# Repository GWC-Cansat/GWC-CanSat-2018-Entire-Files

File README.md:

# GWC CanSat 2017-2018 Files
All completed files used for the 2018 GWC CanSat entry.

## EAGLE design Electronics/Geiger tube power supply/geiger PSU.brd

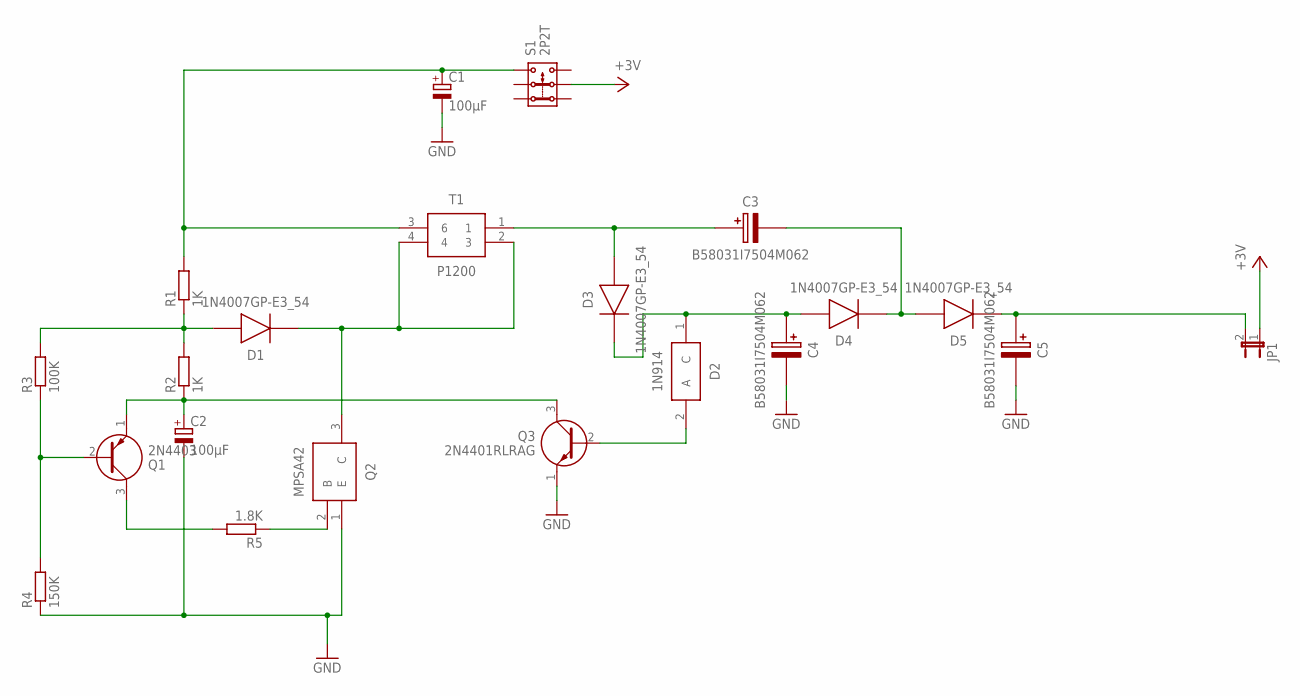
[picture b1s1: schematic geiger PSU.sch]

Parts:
C1, C2: 100μF; 085CS_1AR
C3, C4, C5: B58031I7504M062; CAPPC10878X450N
D1, D3, D4, D5: 1N4007GP-E3_54; DIOAD1405W86L465D235
D2: 1N914; DIO_1N914
JP1: JP1E; JP1
Q1: 2N4403; TO160P419X482X533-3P
Q2: MPSA42; TO127P254X635-3
Q3: 2N4401RLRAG; TO-92
R1, R2: 1K; 0204V
R3: 100K; 0204V
R4: 150K; 0204V
R5: 1.8K; 0204V
S1: 2P2T
T1: P1200; HDRV4W100P762X1270_2X2_1800X18

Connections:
GND: C1.-, C2.-, C4.2 (-), C5.2 (-), Q2.1 (E), Q3.1 (E), R4.1
unnamed: C1.+, R1.2, S1.3.1, T1.3 (6)
unnamed: D1.2 (A), R1.1, R2.2, R3.2
unnamed: Q1.2 (B), R3.1, R4.2
unnamed: C2.+, Q1.1 (E), Q3.3 (C), R2.1
unnamed: Q1.3 (C), R5.2
unnamed: D1.1 (K), Q2.3 (C), T1.2 (3), T1.4
unnamed: C3.1 (+), D3.2 (A), T1.1
unnamed: Q2.2 (B), R5.1
unnamed: D2.2 (A), Q3.2 (B)
unnamed: C4.1 (+), D2.1 (C), D3.1 (K), D4.2 (A)
unnamed: C3.2 (-), D4.1 (K), D5.2 (A)
unnamed: C5.1 (+), D5.1 (K), JP1.2
VCC: JP1.1, S1.2.2

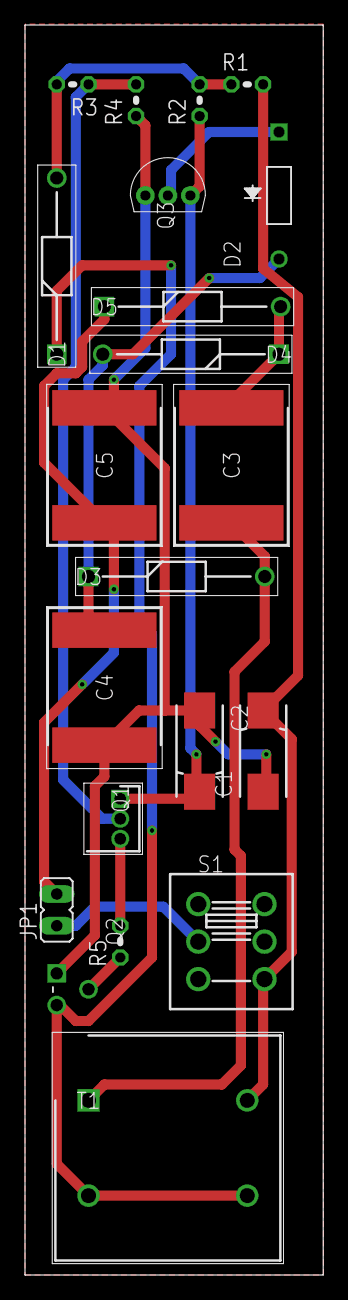
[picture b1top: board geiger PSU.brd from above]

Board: 2 copper layers, 23.9 x 100.0 mm, 21 parts (0 on the bottom side), 14 nets.

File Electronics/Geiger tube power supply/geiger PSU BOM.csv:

"Qty";"Value";"Device";"Package";"Parts";"Description";"3D_PACKAGE";"ALLIED_NUMBER";"DESCRIPTION";"HEIGHT";"MANUFACTURER_NAME";"MANUFACTURER_PART_NUMBER";"OTHER_PART_NUMBER";"RS_PART_NUMBER";"SUPPLIER_NAME";
"1";"";"JP1E";"JP1";"JP1";"JUMPER";"";"";"";"";"";"";"";"";"";
"1";"1.8K";"R-EU_0204/2V";"0204V";"R5";"RESISTOR, European symbol";"";"";"";"";"";"";"";"";"";
"1";"100K";"R-EU_0204/2V";"0204V";"R3";"RESISTOR, European symbol";"";"";"";"";"";"";"";"";"";
"2";"100µF";"CPOL-EU085CS-1AR";"085CS_1AR";"C1, C2";"POLARIZED CAPACITOR, European symbol";"";"";"";"";"";"";"";"";"";
"1";"150K";"R-EU_0204/2V";"0204V";"R4";"RESISTOR, European symbol";"";"";"";"";"";"";"";"";"";
"2";"1K";"R-EU_0204/2V";"0204V";"R1, R2";"RESISTOR, European symbol";"";"";"";"";"";"";"";"";"";
"4";"1N4007GP-E3_54";"1N4007GP-E3_54";"DIOAD1405W86L465D235";"D1, D3, D4, D5";"Vishay 1N4007GP-E3/54, Switching Diode, 1000V 1A, 2000ns, 2-Pin DO-204AL";"";"";"Vishay 1N4007GP-E3/54, Switching Diode, 1000V 1A, 2000ns, 2-Pin DO-204AL";"mm";"Vishay";"1N4007GP-E3/54";"";"7087984P";"RS";
"1";"1N914";"1N914";"DIO_1N914";"D2";"Small Signal Diode";"";"";"Small Signal Diode";"mm";"Fairchild Semiconductor";"1N914";"";"";"RS";
"1";"2N4401RLRAG";"2N4401RLRAG";"TO-92";"Q3";"Transistor NPN 40V 600mA TO92 ON Semi 2N4401RLRAG NPN Bipolar Transistor,  600 mA 40 V, 3-Pin TO-92";"";"70100181";"Transistor NPN 40V 600mA TO92 ON Semi 2N4401RLRAG NPN Bipolar Transistor,  600 mA 40 V, 3-Pin TO-92";"mm";"ON Semiconductor";"2N4401RLRAG";"";"7925476";"RS";
"1";"2N4403";"2N4403";"TO160P419X482X533-3P";"Q1";"MULTICOMP - 2N4403 - TRANSISTOR, PNP, -40V, -0.6A, TO-92";"";"";"MULTICOMP - 2N4403 - TRANSISTOR, PNP, -40V, -0.6A, TO-92";"4.19mm";"MULTICOMP";"2N4403";"";"";"RS";
"1";"2P2T";"2P2T";"2P2T";"S1";"SLIDE SWITCH 2P2T Part No. SS-22F05-G(A)4";"";"";"";"";"";"";"";"";"";
"3";"B58031I7504M062";"B58031I7504M062";"CAPPC10878X450N";"C3, C4, C5";"EPCOS - B58031I7504M062 - CAP, MLCC, AEC-Q200, 0.5UF, 700V, SMD";"";"";"EPCOS - B58031I7504M062 - CAP, MLCC, AEC-Q200, 0.5UF, 700V, SMD";"4.5mm";"EPCOS";"B58031I7504M062";"";"";"RS";
"1";"MPSA42";"MPSA42";"TO127P254X635-3";"Q2";"Transistor";"";"";"Transistor";"mm";"Fairchild Semiconductor";"MPSA42";"";"1241357";"RS";
"1";"P1200";"P1200";"HDRV4W100P762X1270_2X2_1800X18";"T1";"ETAL - P1200 - TRANSFORMER, LINE MATCHING, V.32 BIS";"";"";"ETAL - P1200 - TRANSFORMER, LINE MATCHING, V.32 BIS";"12.6mm";"ETAL";"P1200";"";"";"RS";

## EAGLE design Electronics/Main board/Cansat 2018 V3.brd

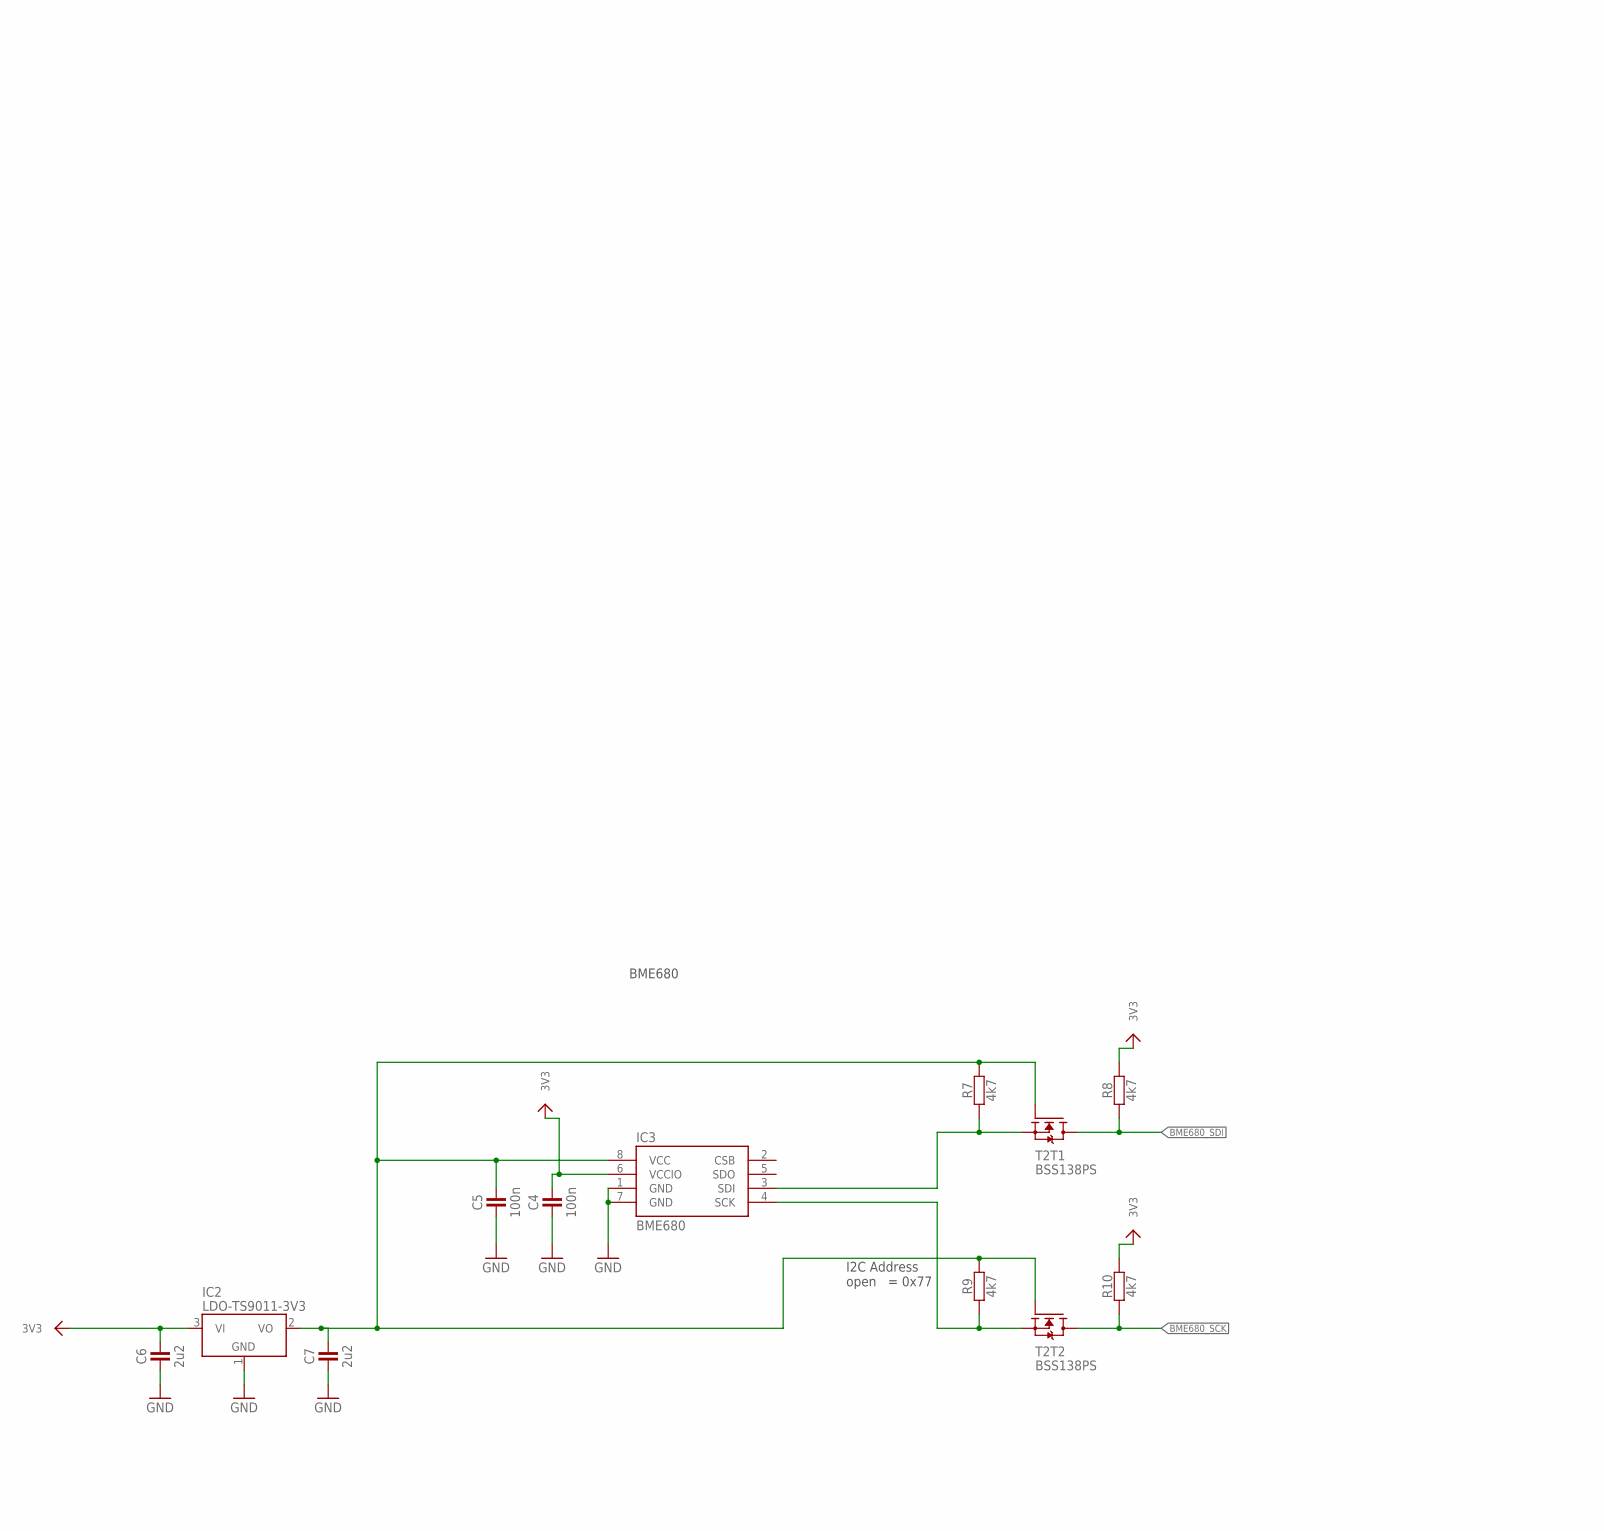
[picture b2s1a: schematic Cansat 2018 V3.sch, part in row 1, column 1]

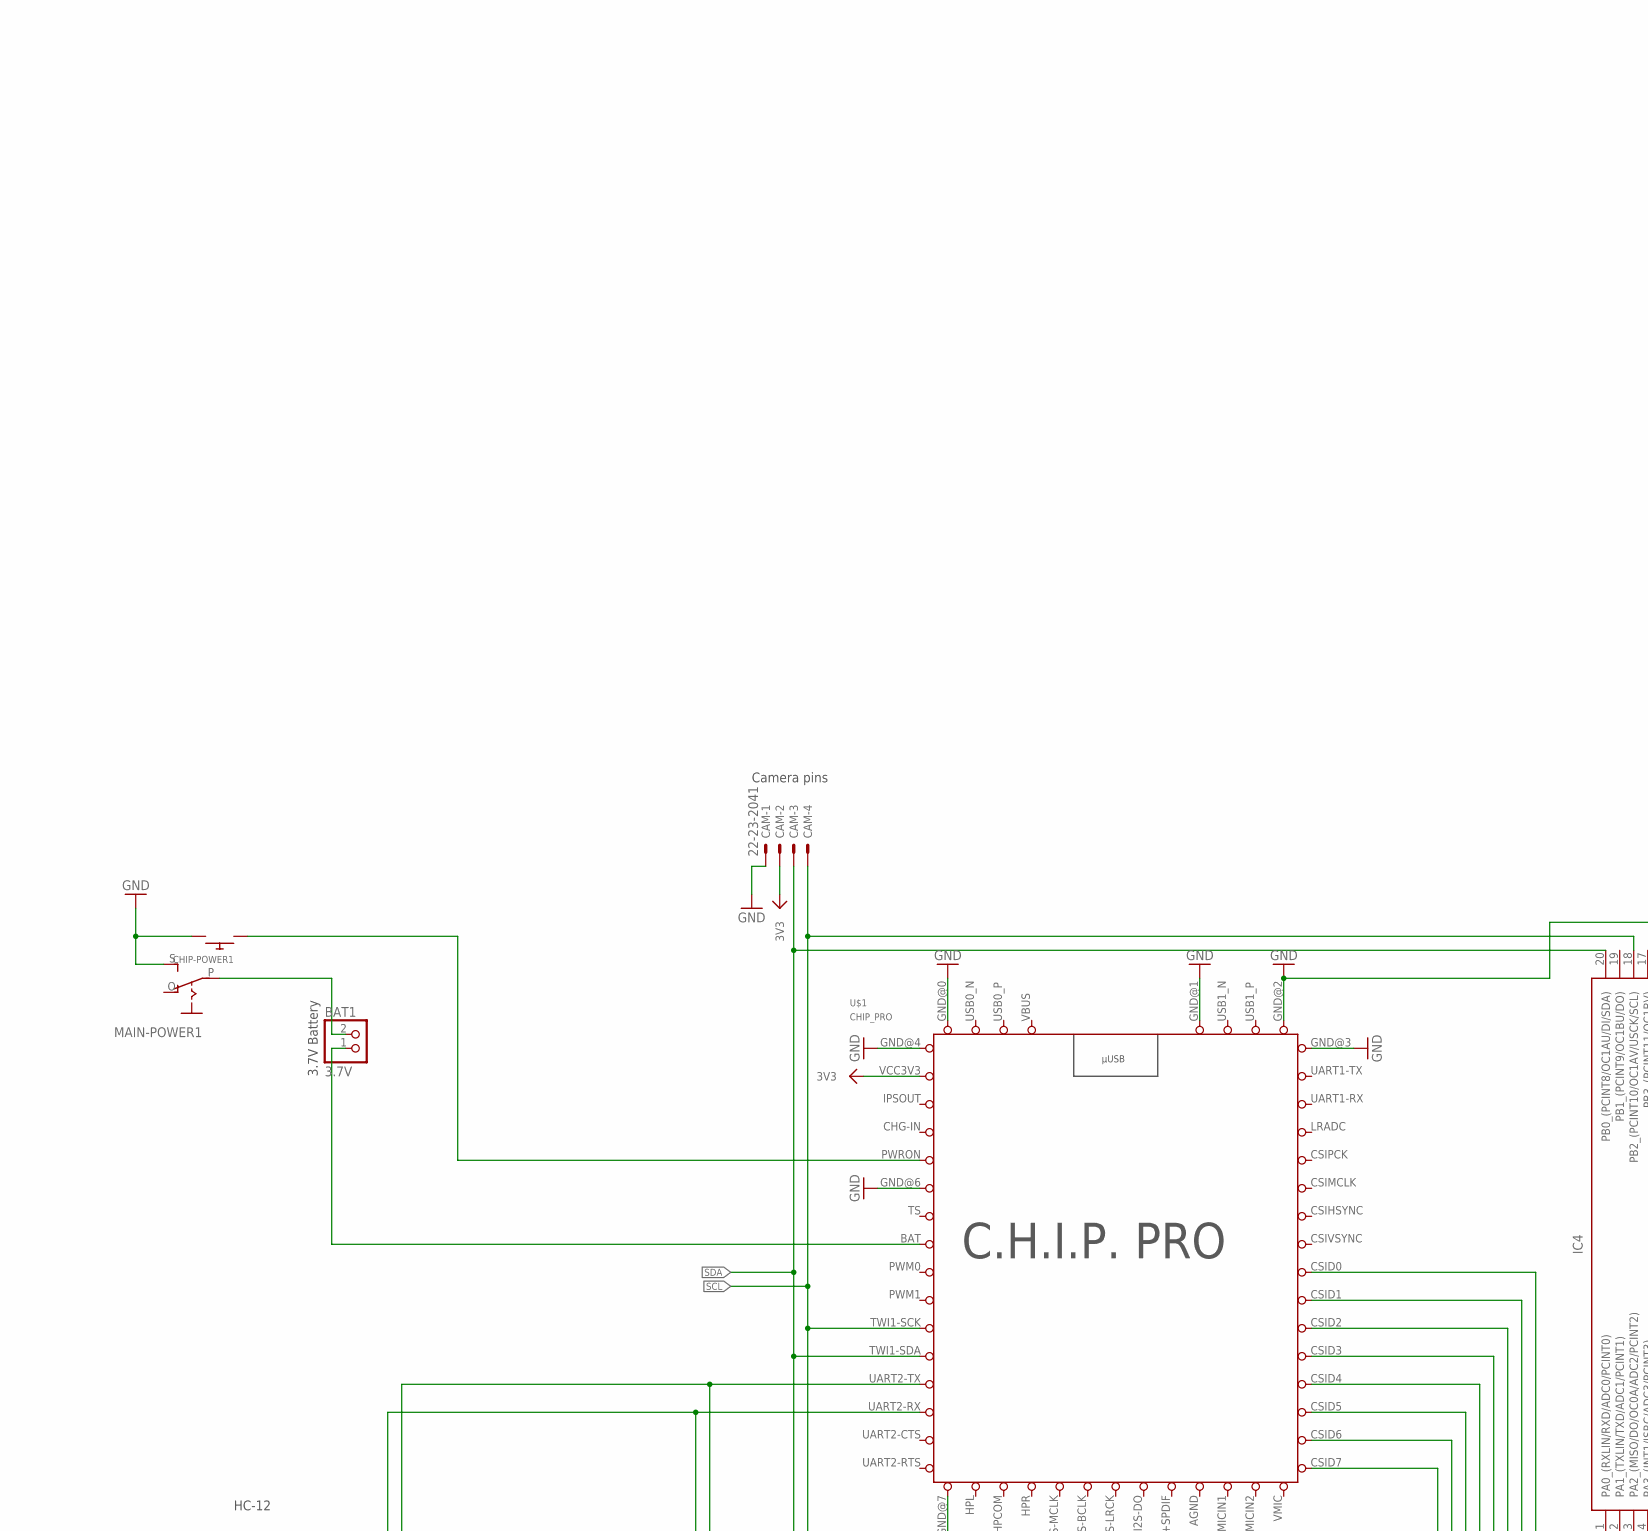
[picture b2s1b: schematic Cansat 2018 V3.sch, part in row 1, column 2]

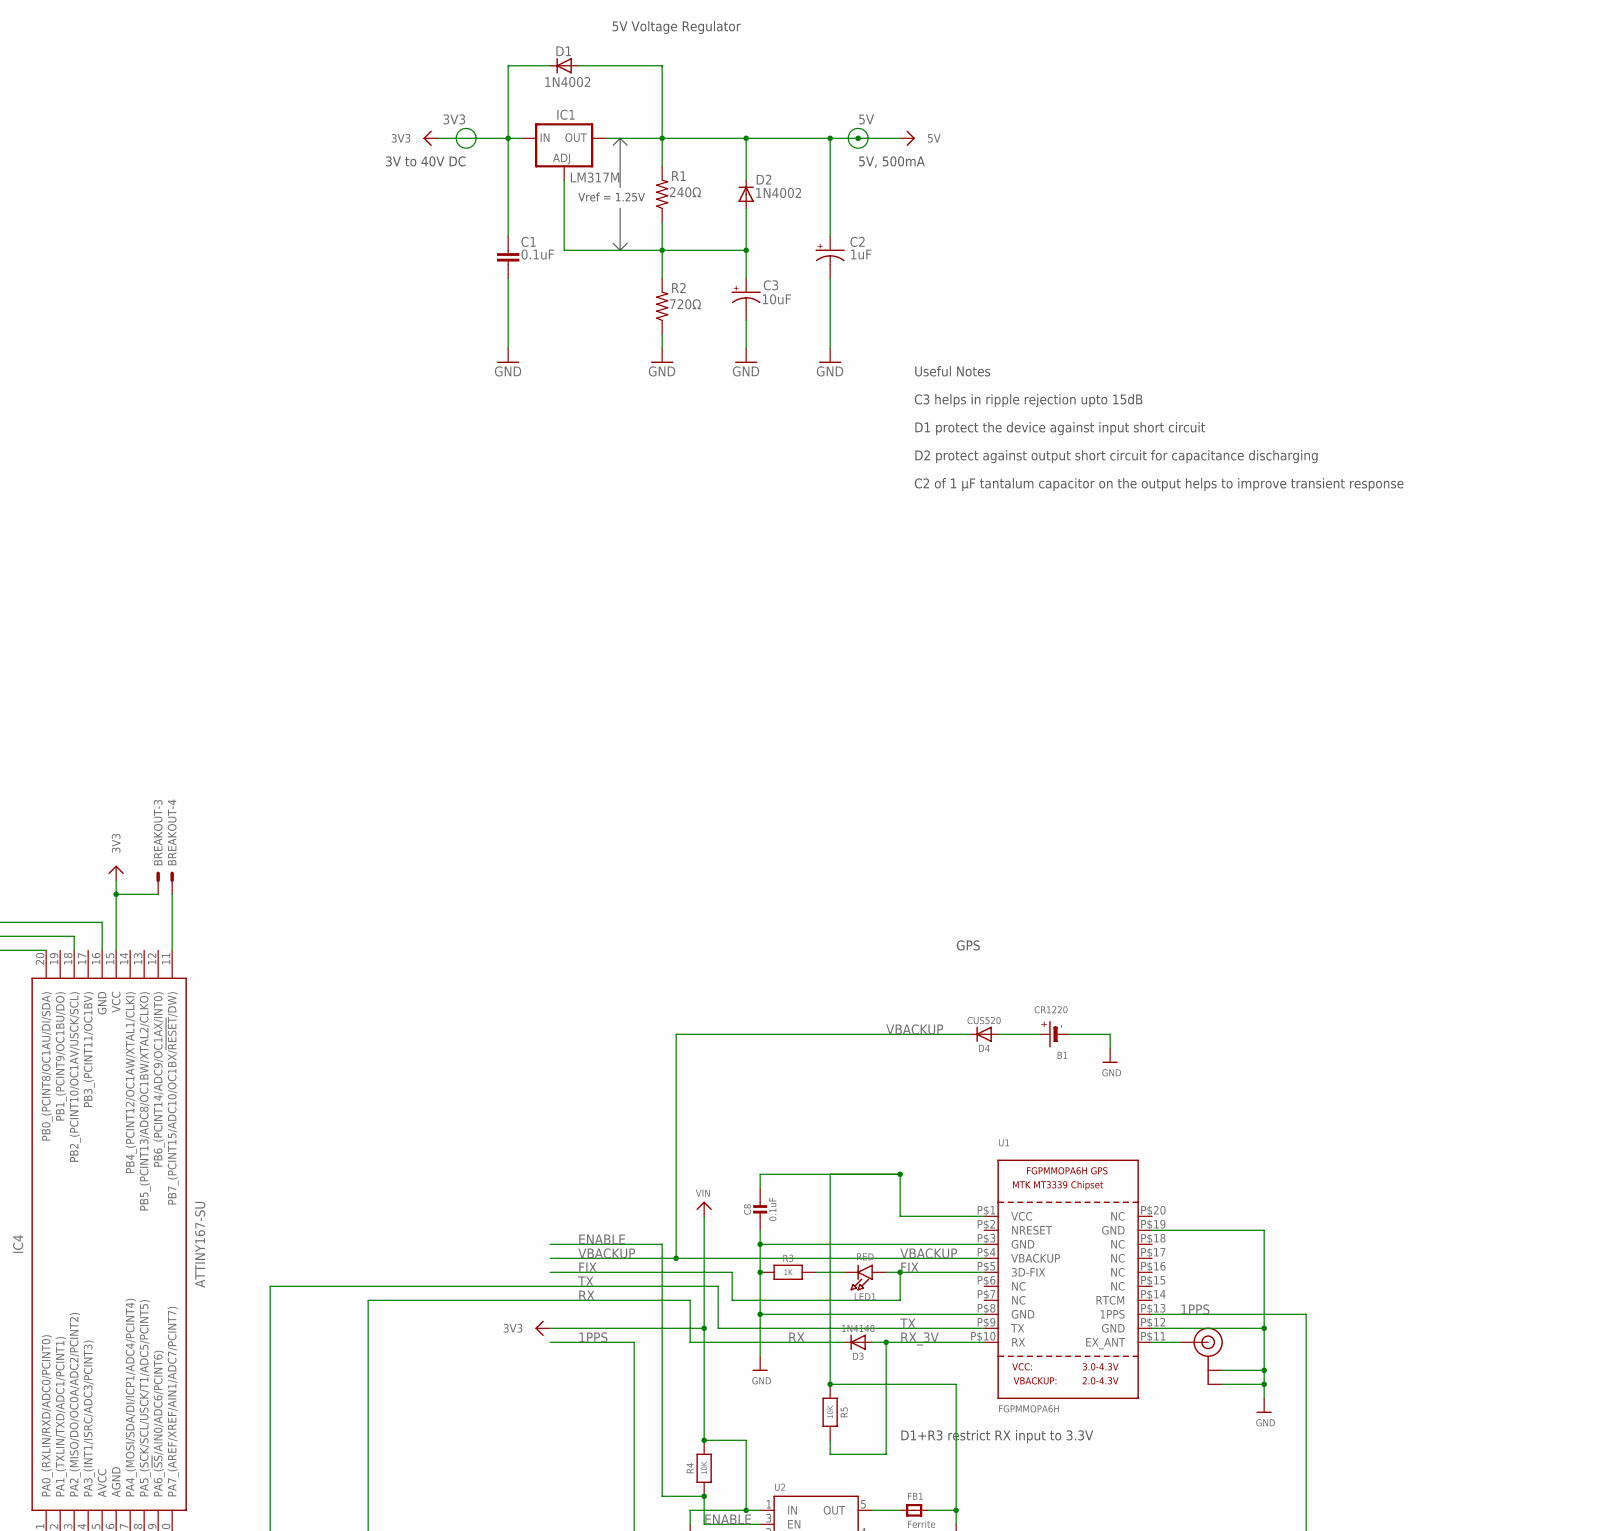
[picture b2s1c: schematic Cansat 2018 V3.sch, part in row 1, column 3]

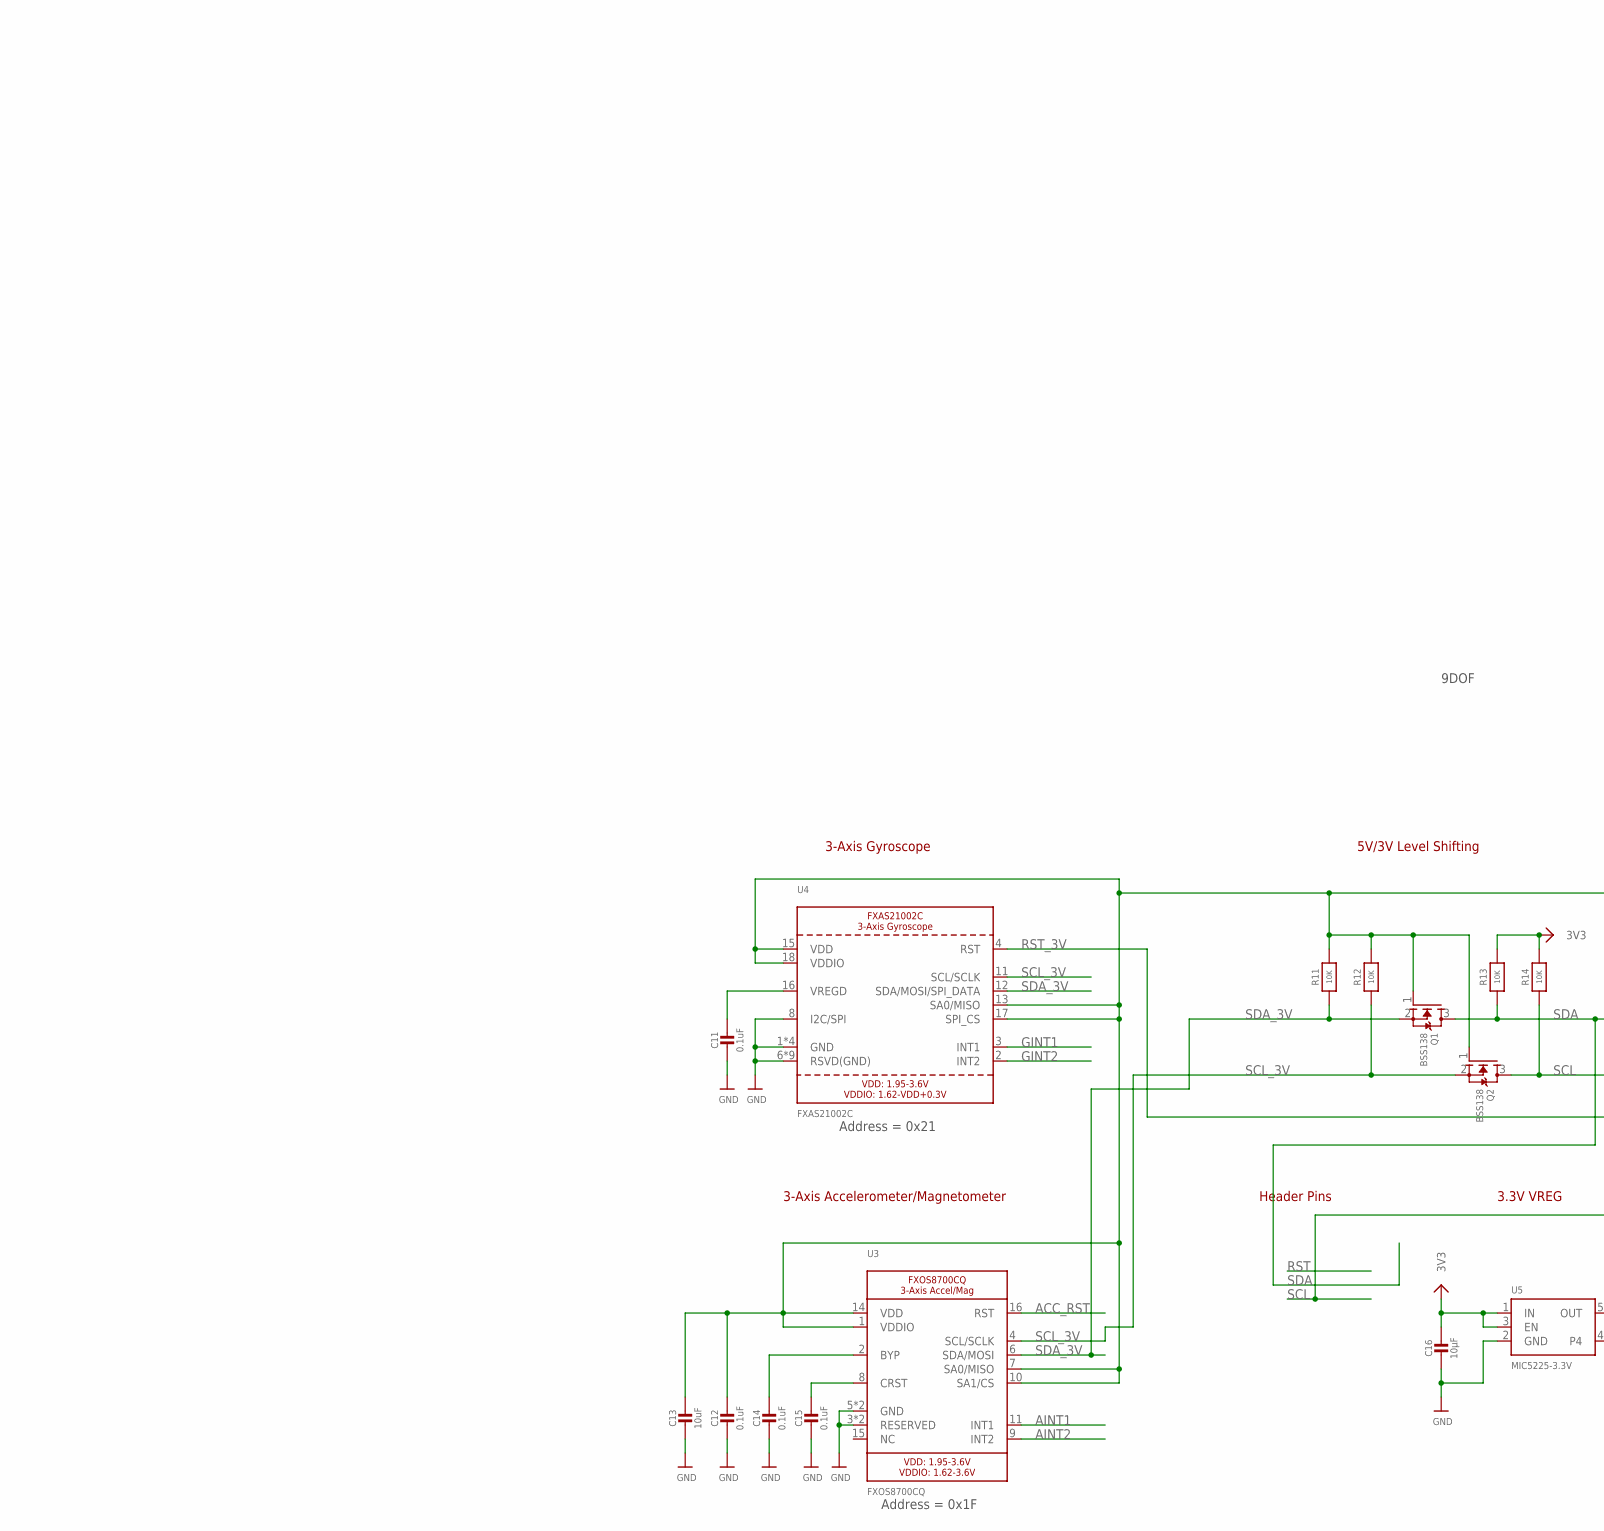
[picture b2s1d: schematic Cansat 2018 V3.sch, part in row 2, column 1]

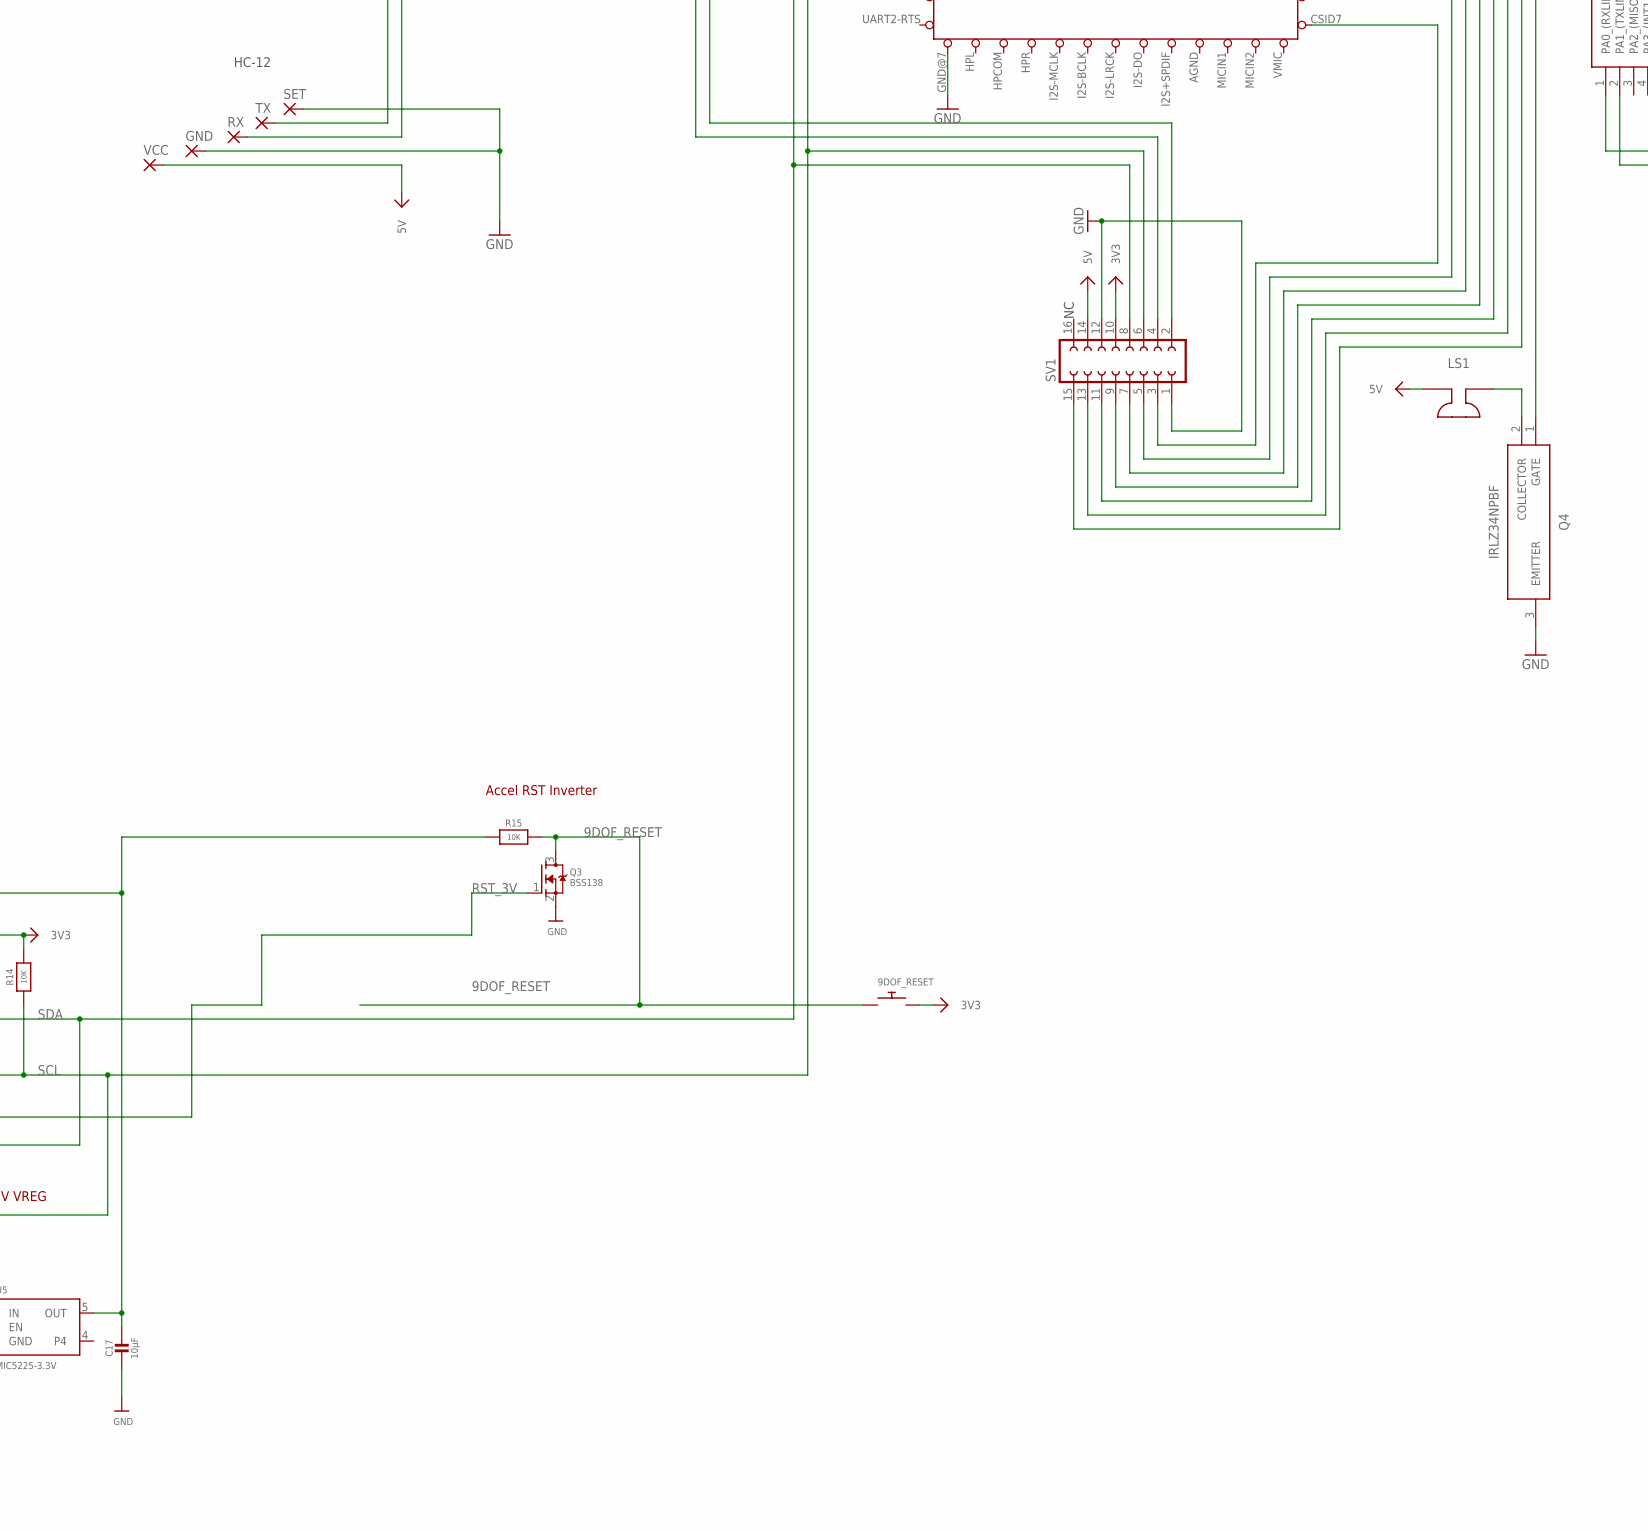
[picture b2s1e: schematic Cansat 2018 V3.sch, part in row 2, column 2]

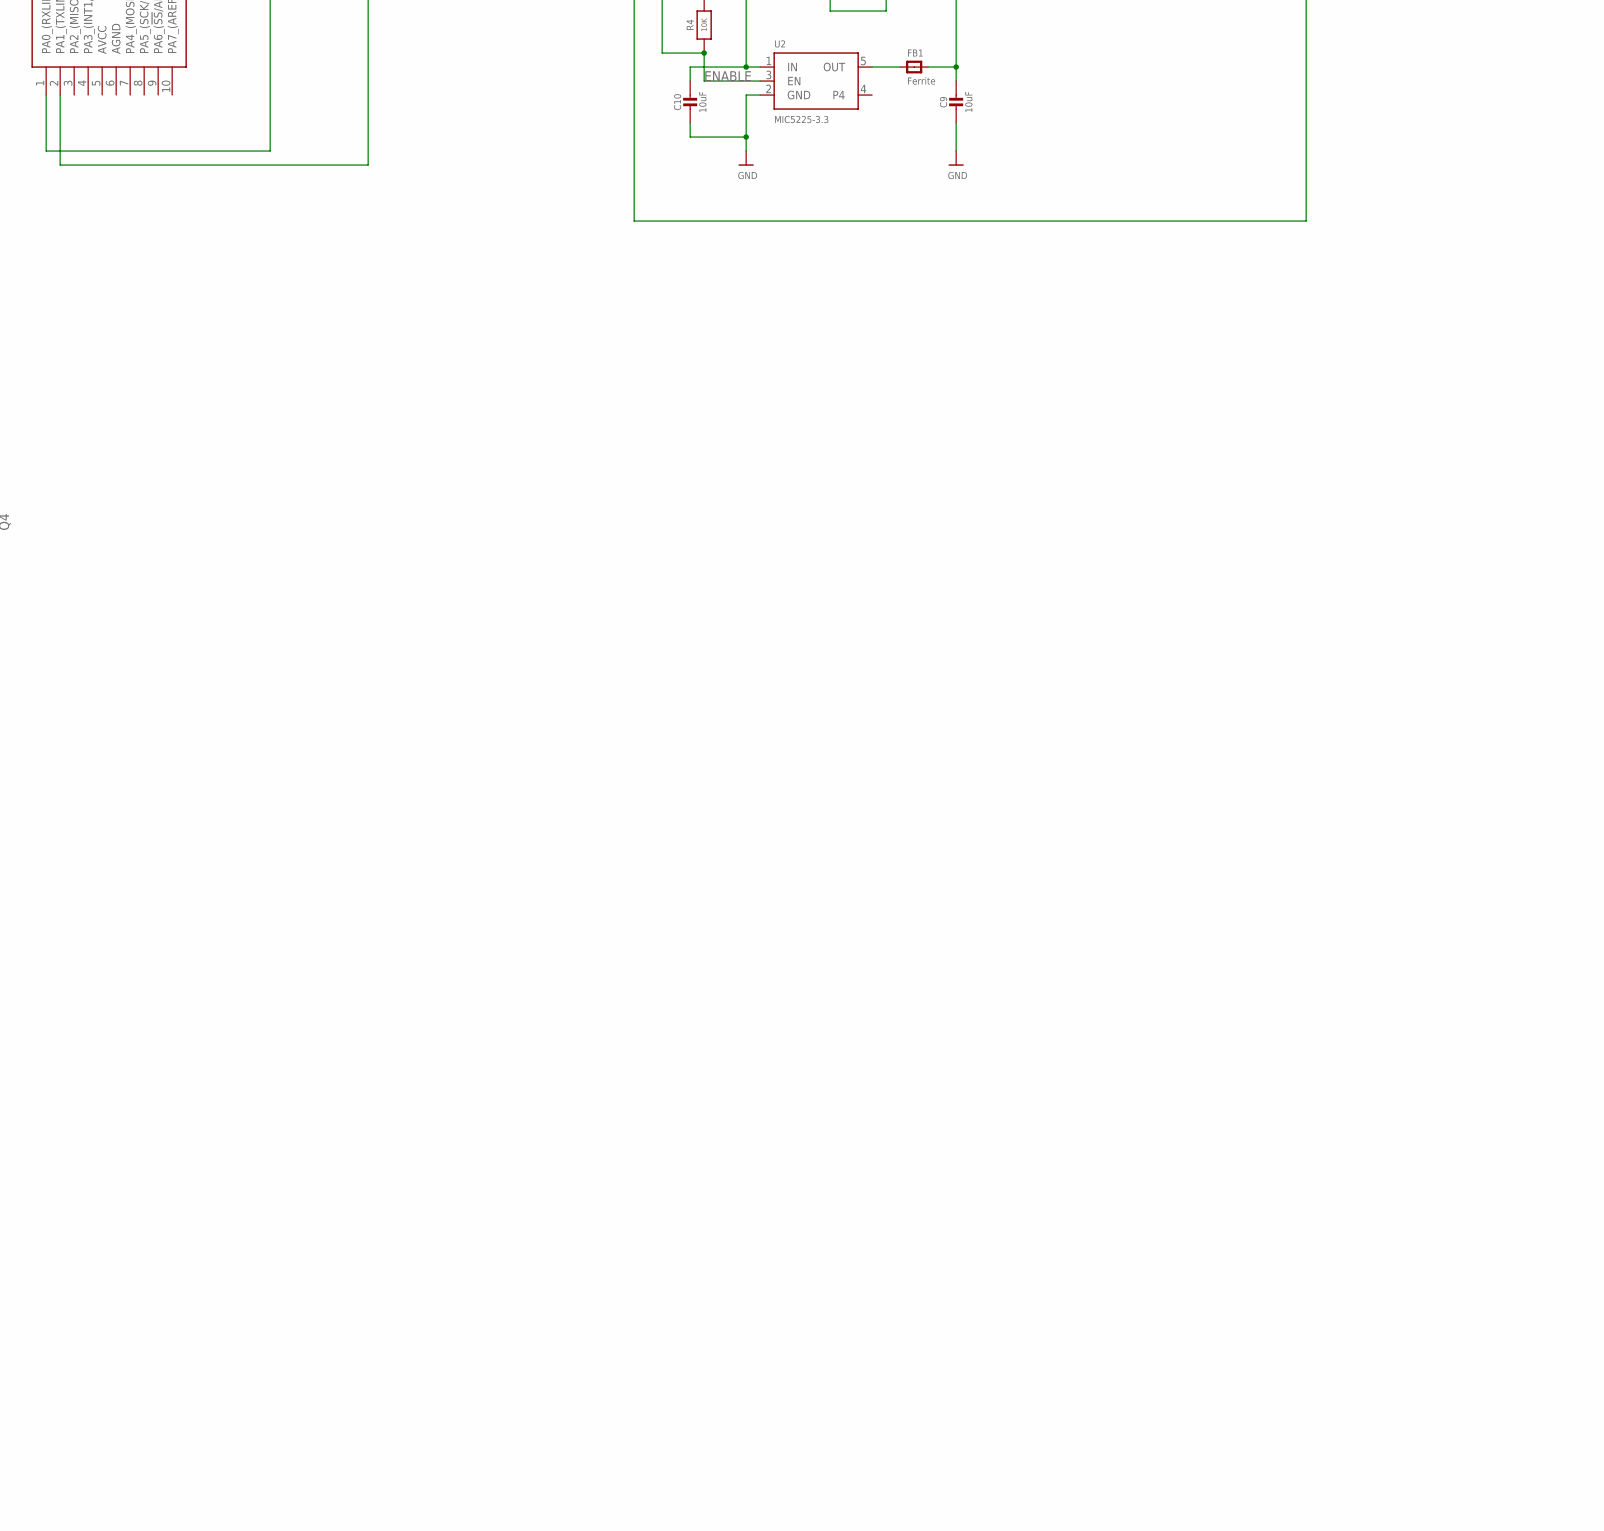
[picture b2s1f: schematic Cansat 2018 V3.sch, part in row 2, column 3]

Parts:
9DOF_RESET: SWITCH_PUSHBUTTONEVQ-PE; TACT_PANA-EVQ
B1: CR1220
BAT1: 3.7V; JST-PH-2-THM-RA
BREAKOUT: 22-23-2041
C1: 0.1uF; C075-052X106
C2: 1uF; 085CS_1AR
C3: 10uF; 085CS_1AR
C4, C5: 100n; C0402
C6, C7: 2u2; C0402
C8, C11, C12, C14, C15: 0.1uF; 0805-NO
C9, C10, C13: 10uF; 0805-NO
C16, C17: 10µF; 0805-NO
CAM: 22-23-2041
CHIP-POWER1: SWITCH_PUSHBUTTONEVQ-PE; TACT_PANA-EVQ
D1, D2: 1N4002; DO41-10
D3: 1N4148; SOD-323
D4: CUS520; SOD-323
FB1: Ferrite; 0805-NO
GND: 2,15/1,0
IC1: LM317MBSTT3; SOT223; PARTNUMBER LM317M
IC2: LDO-TS9011-3V3; SOT23
IC3: BME680
IC4: ATTINY167-SU; SOIC127P1032X265-20N
LED1: RED; CHIPLED_0805
LS1: 3030161; CAPPRD650W70D1200H950
MAIN-POWER1: EG1218S; EG1218
Q1, Q2, Q3: BSS138; SOT23-WIDE
Q4: IRLZ34NPBF; TO254P469X1042X1967-3P
R1: 240Ω; M0805
R2: 720Ω; M0805
R3: 1K; 0805-NO
R4, R5, R11, R12, R13, R14, R15: 10K; 0805-NO
R7, R8, R9, R10: 4k7; C0402
RX: 2,15/1,0
SET: 2,15/1,0
SV1: FE08-2
T2: BSS138PS; SOT363
TX: 2,15/1,0
U1: FGPMMOPA6H
U2: MIC5225-3.3; SOT23-5
U3: FXOS8700CQ; QFN16_3MM_FREESCALE_5X3
U4: FXAS21002C; QFN24_4MM_FREESCALE_7X5
U5: MIC5225-3.3V; SOT23-5
U$1: CHIP_PRO
U$20: U.FL
VCC: 2,15/1,0

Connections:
1PPS: U1.P$13 (1PPS)
3V3: 9DOF_RESET.P$2, BREAKOUT.3, C1.1, C4.2, C6.2, C10.1, C16.1, CAM.2, D1.C, IC1.3 (IN), IC2.3 (VI), IC3.6 (VCCIO), IC4.15 (VCC), R4.2, R8.2, R10.2, R13.2, R14.2, SV1.10, U2.1 (IN), U5.1 (IN), U5.3 (EN), U$1.VCC3V3
5V: C2.+, D1.A, D2.C, IC1.4 (OUT), LS1.1 (+), R1.2, SV1.14, VCC.1
9DOF_RESET: 9DOF_RESET.P$1, Q3.3 (D), R15.2
ACC_RST: U3.16 (RST)
AGND: IC4.6 (AGND), U$1.AGND
AINT1: U3.11 (INT1)
AINT2: U3.9 (INT2)
BME680_LV_SCK: IC3.4 (SCK), R9.1, T2.4 (S)
BME680_LV_SDI: IC3.3 (SDI), R7.1, T2.1 (S)
BME680_SCK: R10.1, T2.3 (D)
BME680_SDI: R8.1, T2.6 (D)
CHG-IN: U$1.CHG-IN
ENABLE: R4.1, U2.3 (EN)
FIX: LED1.A, U1.P$5 (3D-FIX)
GINT1: U4.3 (INT1)
GINT2: U4.2 (INT2)
GND: B1.-, C1.2, C2.-, C3.-, C4.1, C5.1, C6.1, C7.1, C8.2, C9.2, C10.2, C11.2, C12.2, C13.2, C14.2, C15.2, C16.2, C17.2, CAM.1, CHIP-POWER1.P$2, GND.1, IC2.1 (GND), IC3.1 (GND), IC3.7 (GND), IC4.16 (GND), MAIN-POWER1.S, Q3.2 (S), Q4.3 (EMITTER), R2.1, R3.1, SET.1, SV1.1, SV1.12, U1.P$3 (GND), U1.P$8 (GND), U1.P$12 (GND), U1.P$19 (GND), U2.2 (GND), U3.3 (RESERVED), U3.5 (GND), U3.12 (GND), U3.13 (RESERVED), U4.1 (GND), U4.5 (GND), U4.6 (RSVD(GND)), U4.7 (RSVD(GND)), U4.8 (I2C/SPI), U4.9 (RSVD(GND)), U4.10 (RSVD(GND)), U4.14 (GND), U4.19 (GND), U4.20 (RSVD(GND)), U4.21 (RSVD(GND)), U4.22 (RSVD(GND)), U4.23 (RSVD(GND)), U4.24 (RSVD(GND)), U5.2 (GND), U$1.GND@0 (GND), U$1.GND@1 (GND), U$1.GND@2 (GND), U$1.GND@3 (GND), U$1.GND@4 (GND), U$1.GND@6 (GND), U$1.GND@7 (GND), U$20.P$1 (GND), U$20.P$2 (GND)
IPSOUT: U$1.IPSOUT
unnamed: C3.+, D2.A, IC1.1 (ADJ), R1.1, R2.2
unnamed: LED1.C, R3.2
unnamed: FB1.1, U2.5 (OUT)
unnamed: SV1.4, TX.1, U$1.UART2-RX
unnamed: C5.2, C7.2, IC2.2 (VO), IC3.8 (VCC), R7.2, R9.2, T2.2 (G), T2.5 (G)
unnamed: RX.1, SV1.2, U$1.UART2-TX
unnamed: B1.+$1 (+), B1.+$2 (+), D4.A
unnamed: C8.1, C9.1, FB1.2, R5.1, U1.P$1 (VCC)
unnamed: U1.P$11 (EX_ANT), U$20.P$3 (SIGNAL)
unnamed: BREAKOUT.4, IC4.11 (PB7_(PCINT15/ADC10/OC1BX/!RESET!/DW))
unnamed: C11.1, U4.16 (VREGD)
unnamed: CHIP-POWER1.P$1, U$1.PWRON
unnamed: LS1.2 (-), Q4.2 (COLLECTOR)
unnamed: BAT1.2 (1), MAIN-POWER1.P
unnamed: Q4.1 (GATE), U$1.CSID0
unnamed: SV1.15, U$1.CSID1
unnamed: BAT1.1 (2), U$1.BAT
unnamed: SV1.13, U$1.CSID2
unnamed: SV1.11, U$1.CSID3
unnamed: SV1.9, U$1.CSID4
unnamed: SV1.7, U$1.CSID5
unnamed: C14.1, U3.2 (BYP)
unnamed: SV1.5, U$1.CSID6
unnamed: C15.1, U3.8 (CRST)
unnamed: SV1.3, U$1.CSID7
OUT: C12.1, C13.1, C17.1, Q1.1 (G), Q2.1 (G), R11.2, R12.2, R15.1, U3.1 (VDDIO), U3.7 (SA0/MISO), U3.10 (SA1/CS), U3.14 (VDD), U4.13 (SA0/MISO), U4.15 (VDD), U4.17 (SPI_CS), U4.18 (VDDIO), U5.5 (OUT)
RST_3V: Q3.1 (G), U4.4 (RST)
RX: D3.C, IC4.2 (PA1_(TXLIN/TXD/ADC1/PCINT1))
RX_3V: D3.A, R5.2, U1.P$10 (RX)
SCL: CAM.4, IC4.18 (PB2_(PCINT10/OC1AV/USCK/SCL)), Q2.3 (D), R14.1, SV1.6, U$1.TWI1-SCK
SCL_3V: Q2.2 (S), R12.1, U3.4 (SCL/SCLK), U4.11 (SCL/SCLK)
SDA: CAM.3, IC4.20 (PB0_(PCINT8/OC1AU/DI/SDA)), Q1.3 (D), R13.1, SV1.8, U$1.TWI1-SDA
SDA_3V: Q1.2 (S), R11.1, U3.6 (SDA/MOSI), U4.12 (SDA/MOSI/SPI_DATA)
TX: IC4.1 (PA0_(RXLIN/RXD/ADC0/PCINT0)), U1.P$9 (TX)
VBACKUP: D4.C, U1.P$4 (VBACKUP)
VBUS: U$1.VBUS

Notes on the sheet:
5V Voltage Regulator
C3 helps in ripple rejection upto 15dB
D1 protect the device against input short circuit
D2 protect against output short circuit for capacitance discharging
C2 of 1 µF tantalum capacitor on the output helps to improve transient response
Useful Notes
5V, 500mA
3V to 40V DC
Vref = 1.25V
Camera pins
I2C Address open = 0x77
BME680
D1+R3 restrict RX input to 3.3V
Address = 0x21
Address = 0x1F
3-Axis Accelerometer/Magnetometer
3-Axis Gyroscope
5V/3V Level Shifting
3.3V VREG
Header Pins
Accel RST Inverter
3.7V Battery
9DOF
GPS
HC-12
